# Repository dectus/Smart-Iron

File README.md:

# Smart-Iron
An arduino based controller for precisely controlling the temperature of a clothes iron for heat shrinking fabric covering on aircraft.

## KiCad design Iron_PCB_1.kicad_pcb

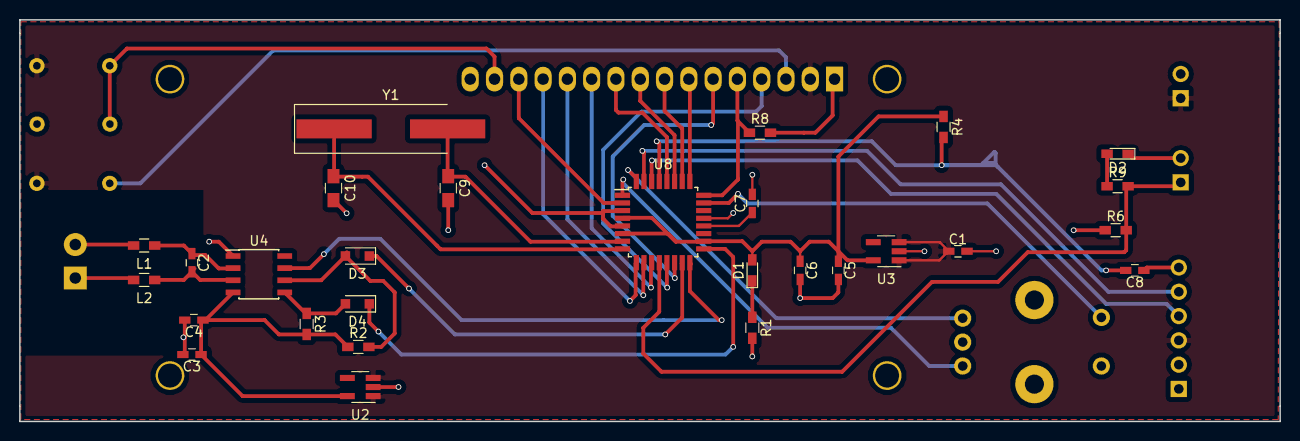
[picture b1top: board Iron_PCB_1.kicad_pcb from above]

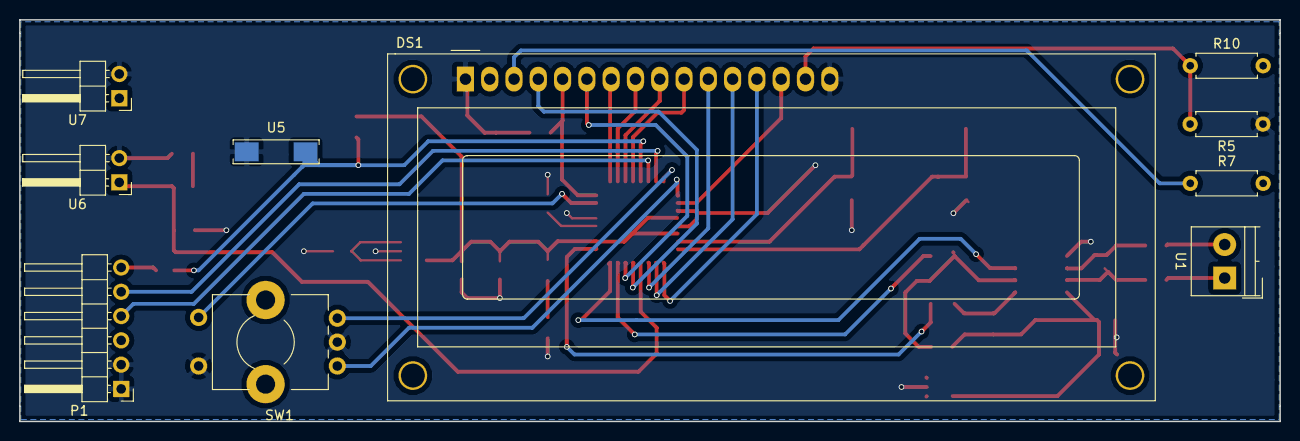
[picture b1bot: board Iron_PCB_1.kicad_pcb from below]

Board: 2 copper layers, 131.8 x 42.0 mm, 38 parts (10 on the bottom side), 39 nets.

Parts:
C1, C3, C4, C5: 10μF; C_0603_HandSoldering
C2: 10nF; C_0603_HandSoldering
C6, C7, C8: 0.1μF; C_0603_HandSoldering
C9, C10: 18pF; C_0805_HandSoldering
D1, D2: LED; LED_0603_HandSoldering
D3, D4: D; D_SOD-323_HandSoldering
DS1: WC1602A
L1, L2: Ferrite_Bead_Small; L_0603_HandSoldering
P1: CONN_01X06; Pin_Header_Angled_1x06_Pitch2.54mm
R1, R2, R3, R4, R6, R8: 10K; R_0603_HandSoldering
R5: B; R_Axial_DIN0207_L6.3mm_D2.5mm_P7.62mm_Horizontal
R7: C; R_Axial_DIN0207_L6.3mm_D2.5mm_P7.62mm_Horizontal
R9: 330; R_0603_HandSoldering
R10: A; R_Axial_DIN0207_L6.3mm_D2.5mm_P7.62mm_Horizontal
SW1: Rotary_Encoder_Switch; En11_Encoder
U1: TERM_BLOCK; TerminalBlock_4UCON_19963_02x3.5mm_Straight
U2: LP2985; SOT-23-5_HandSoldering
U3: MIC5205; SOT-23-5_HandSoldering
U4: MAX31855; SOIC-8_3.9x4.9mm_Pitch1.27mm
U5: Button; SW_SPST_REED_CT05-XXXX-J1
U6, U7: PLUG; Pin_Header_Angled_1x02_Pitch2.54mm
U8: ATMEGA328P-AU; TQFP-32_7x7mm_Pitch0.8mm
Y1: Crystal; Crystal_SMD_HC49-SD_HandSoldering

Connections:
3.3V: C3.1, C4.1, R2.1, R3.2, U2.4, U4.4
5V: C5.1, C6.1, D1.2, R4.1, U3.5, U8.4, U8.6, U8.18
A0: SW1.4, U8.23
A1: DS1.5, R8.1, U8.24
A2: DS1.7, U8.25
A3: DS1.8, U8.26
A4: DS1.9, U8.27
A5: DS1.10, U8.28
D2: SW1.1, U8.32
D3: SW1.3, U8.1
D4: DS1.14, U8.2
D5: DS1.13, U8.9
D6: DS1.12, U8.10
D7: DS1.11, U8.11
D9: DS1.4, U8.13
D10: DS1.6, U8.14
DTR: C8.1, P1.6
GND: C1.2, C3.2, C4.2, C5.2, C6.2, C7.2, C9.2, C10.2, D2.1, DS1.1, DS1.16, P1.1, P1.2, R1.2, R5.1, R6.1, R8.2, SW1.2, SW1.5, U2.2, U3.2, U4.1, U5.2, U6.2, U7.2, U8.3, U8.5, U8.21
MISO: U4.7, U8.16
MOSI: D3.1, U8.15
unnamed: C2.1, L1.1, U4.2
unnamed: C2.2, L2.1, U4.3
unnamed: C7.1, U8.20
unnamed: C8.2, R4.2, U5.1, U8.29
unnamed: C9.1, U8.7, Y1.2
unnamed: C10.1, U8.8, Y1.1
unnamed: D1.1, R1.1
unnamed: D2.2, R9.1
unnamed: D3.2, R2.2, U4.6
unnamed: D4.2, R3.1, U4.5
unnamed: DS1.3, R7.1
unnamed: DS1.15, R5.2, R10.1
unnamed: L1.2, U1.2
unnamed: L2.2, U1.1
RX1: P1.4, U8.30
SCK: D4.1, U8.17
SSR: R6.2, R9.2, U6.1, U8.12
TX0: P1.5, U8.31
Vcc: C1.1, DS1.2, P1.3, R7.2, R10.2, U2.1, U2.3, U3.1, U3.3, U7.1
